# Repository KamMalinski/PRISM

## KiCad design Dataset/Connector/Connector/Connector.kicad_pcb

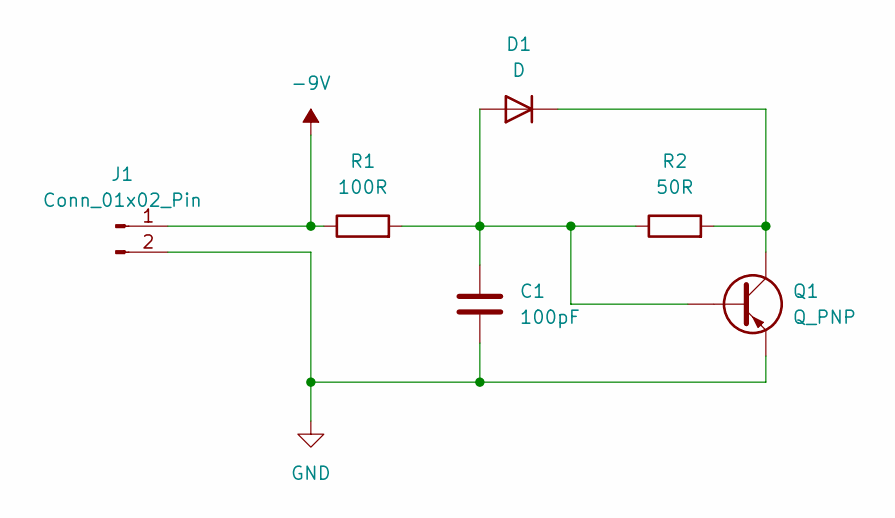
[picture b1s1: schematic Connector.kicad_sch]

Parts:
C1: 100pF; C_Radial_D12.5mm_H20.0mm_P5.00mm
D1: D; D_DO-201_P15.24mm_Horizontal
J1: Conn_01x02_Pin; PinSocket_1x02_P2.00mm_Vertical
Q1: Q_PNP; TO-92L_Wide
R1: 100R; R_Axial_DIN0614_L14.3mm_D5.7mm_P25.40mm_Horizontal
R2: 50R; R_Axial_Power_L25.0mm_W9.0mm_P30.48mm

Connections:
-9V: J1.1, R1.1
GND: C1.2, J1.2, Q1.3
unnamed: C1.1, D1.2 (A), Q1.2, R1.2, R2.1
unnamed: D1.1 (K), Q1.1, R2.2

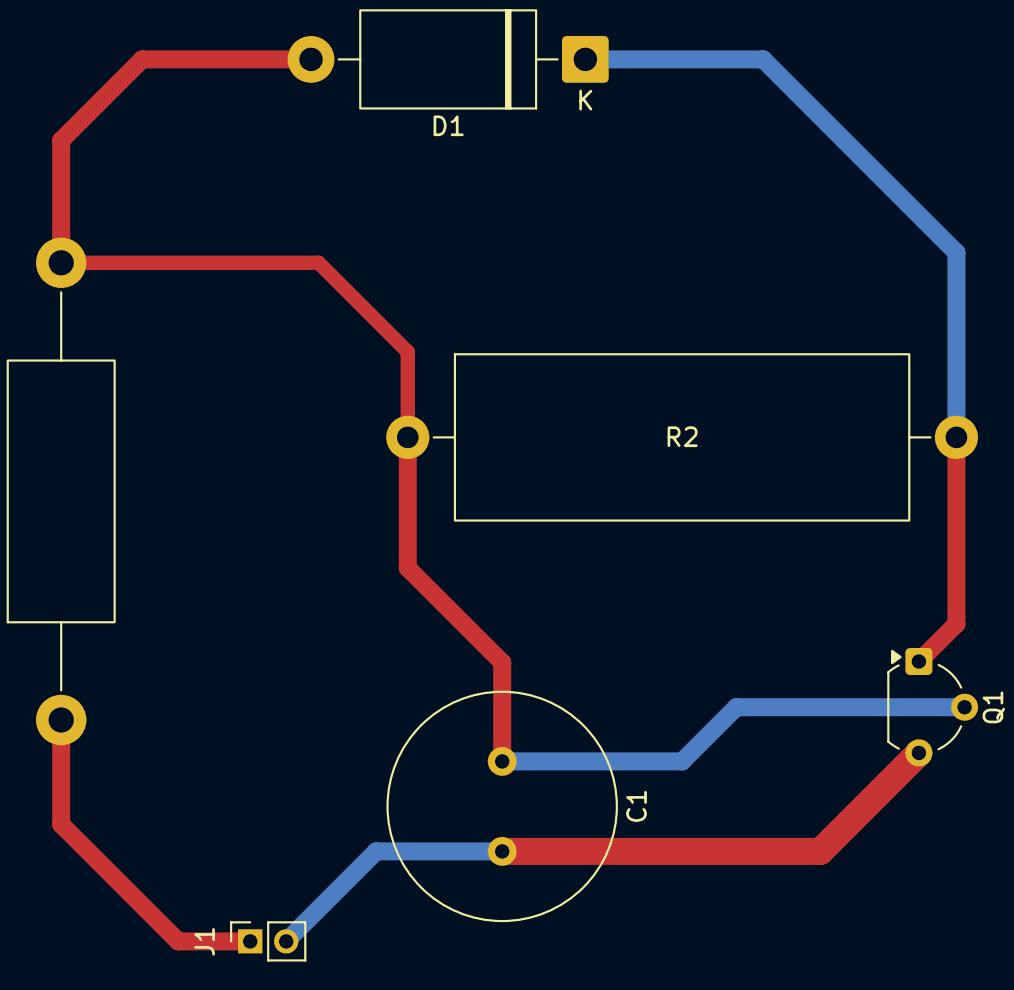
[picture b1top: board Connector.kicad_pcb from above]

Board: 2 copper layers, 6 parts (0 on the bottom side), 4 nets.

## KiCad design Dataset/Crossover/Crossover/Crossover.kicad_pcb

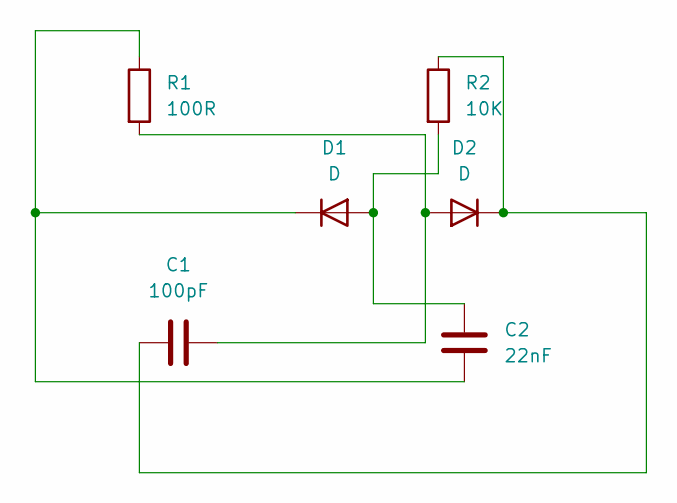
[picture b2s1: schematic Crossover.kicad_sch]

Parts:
C1: 100pF; C_Radial_D16.0mm_H25.0mm_P7.50mm
C2: 22nF; C_Radial_D12.5mm_H25.0mm_P5.00mm
D1, D2: D; D_5KP_P12.70mm_Horizontal
R1: 100R; R_Axial_Power_L20.0mm_W6.4mm_P22.40mm
R2: 10K; R_Axial_Power_L20.0mm_W6.4mm_P22.40mm

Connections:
unnamed: C2.1, D1.2 (A), R2.2
unnamed: C2.2, D1.1 (K), R1.1
unnamed: C1.2, D2.2 (A), R1.2
unnamed: C1.1, D2.1 (K), R2.1

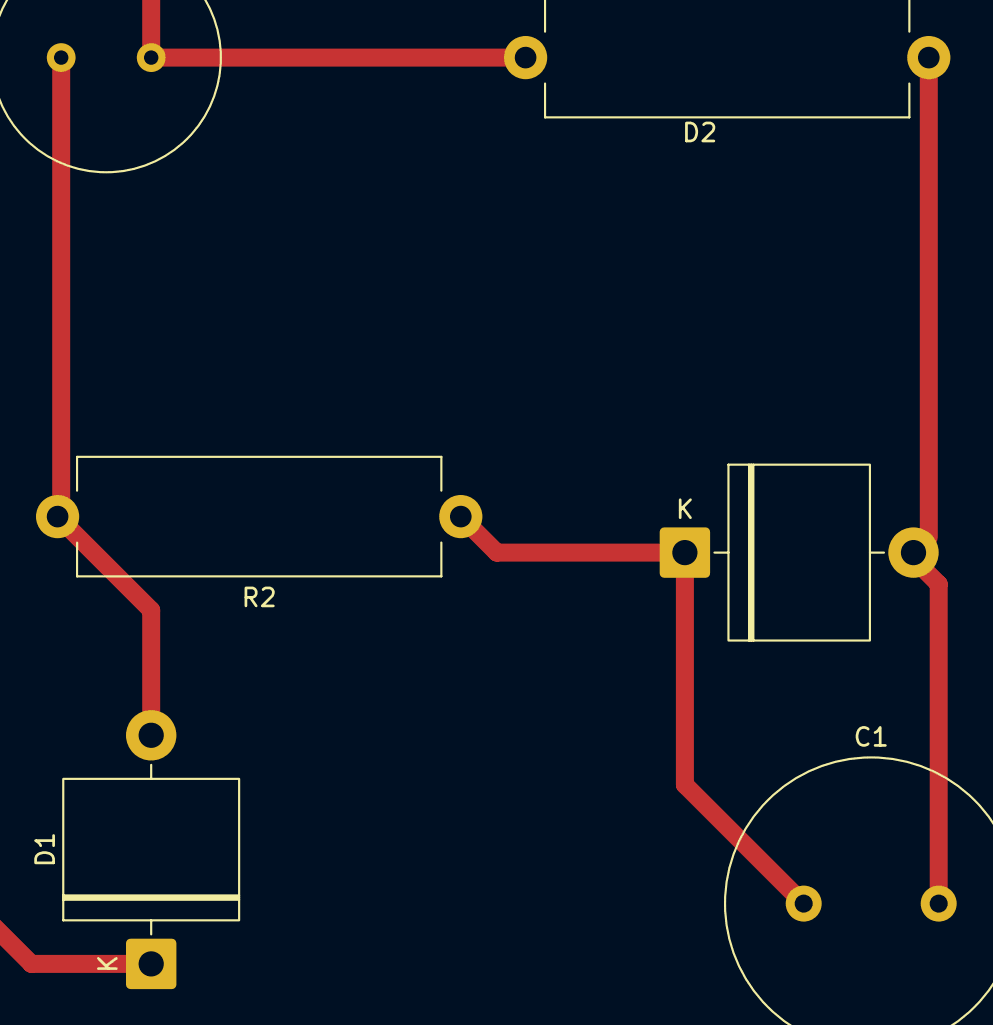
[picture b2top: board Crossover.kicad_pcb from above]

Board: 2 copper layers, 6 parts (0 on the bottom side), 4 nets.

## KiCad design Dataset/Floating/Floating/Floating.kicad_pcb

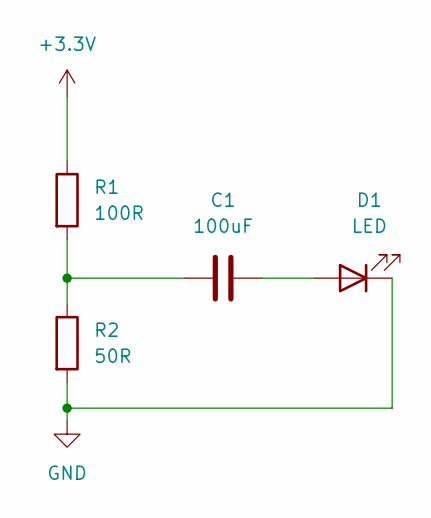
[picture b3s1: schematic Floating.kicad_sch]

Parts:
C1: 100uF; CP_Radial_Tantal_D8.0mm_P2.50mm
D1: LED; LED_D10.0mm
R1: 100R; R_Axial_DIN0309_L9.0mm_D3.2mm_P12.70mm_Horizontal
R2: 50R; R_Axial_DIN0411_L9.9mm_D3.6mm_P5.08mm_Vertical

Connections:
+3.3V: R1.1
GND: D1.1 (K), R2.2
unnamed: C1.1, R1.2, R2.1
unnamed: C1.2, D1.2 (A)

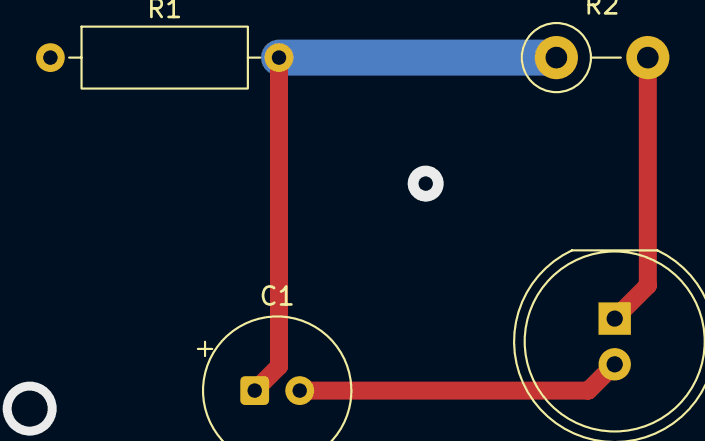
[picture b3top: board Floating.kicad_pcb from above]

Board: 2 copper layers, 4 parts (0 on the bottom side), 3 nets.
